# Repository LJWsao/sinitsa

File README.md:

KiCAD files for the all band receiver. This can pick up strong local sources of RF such as AM and FM radio stations. It is based on the 
Amazing All Band Receiver by Charles Wenzel: https://techlib.com/electronics/allband.htm

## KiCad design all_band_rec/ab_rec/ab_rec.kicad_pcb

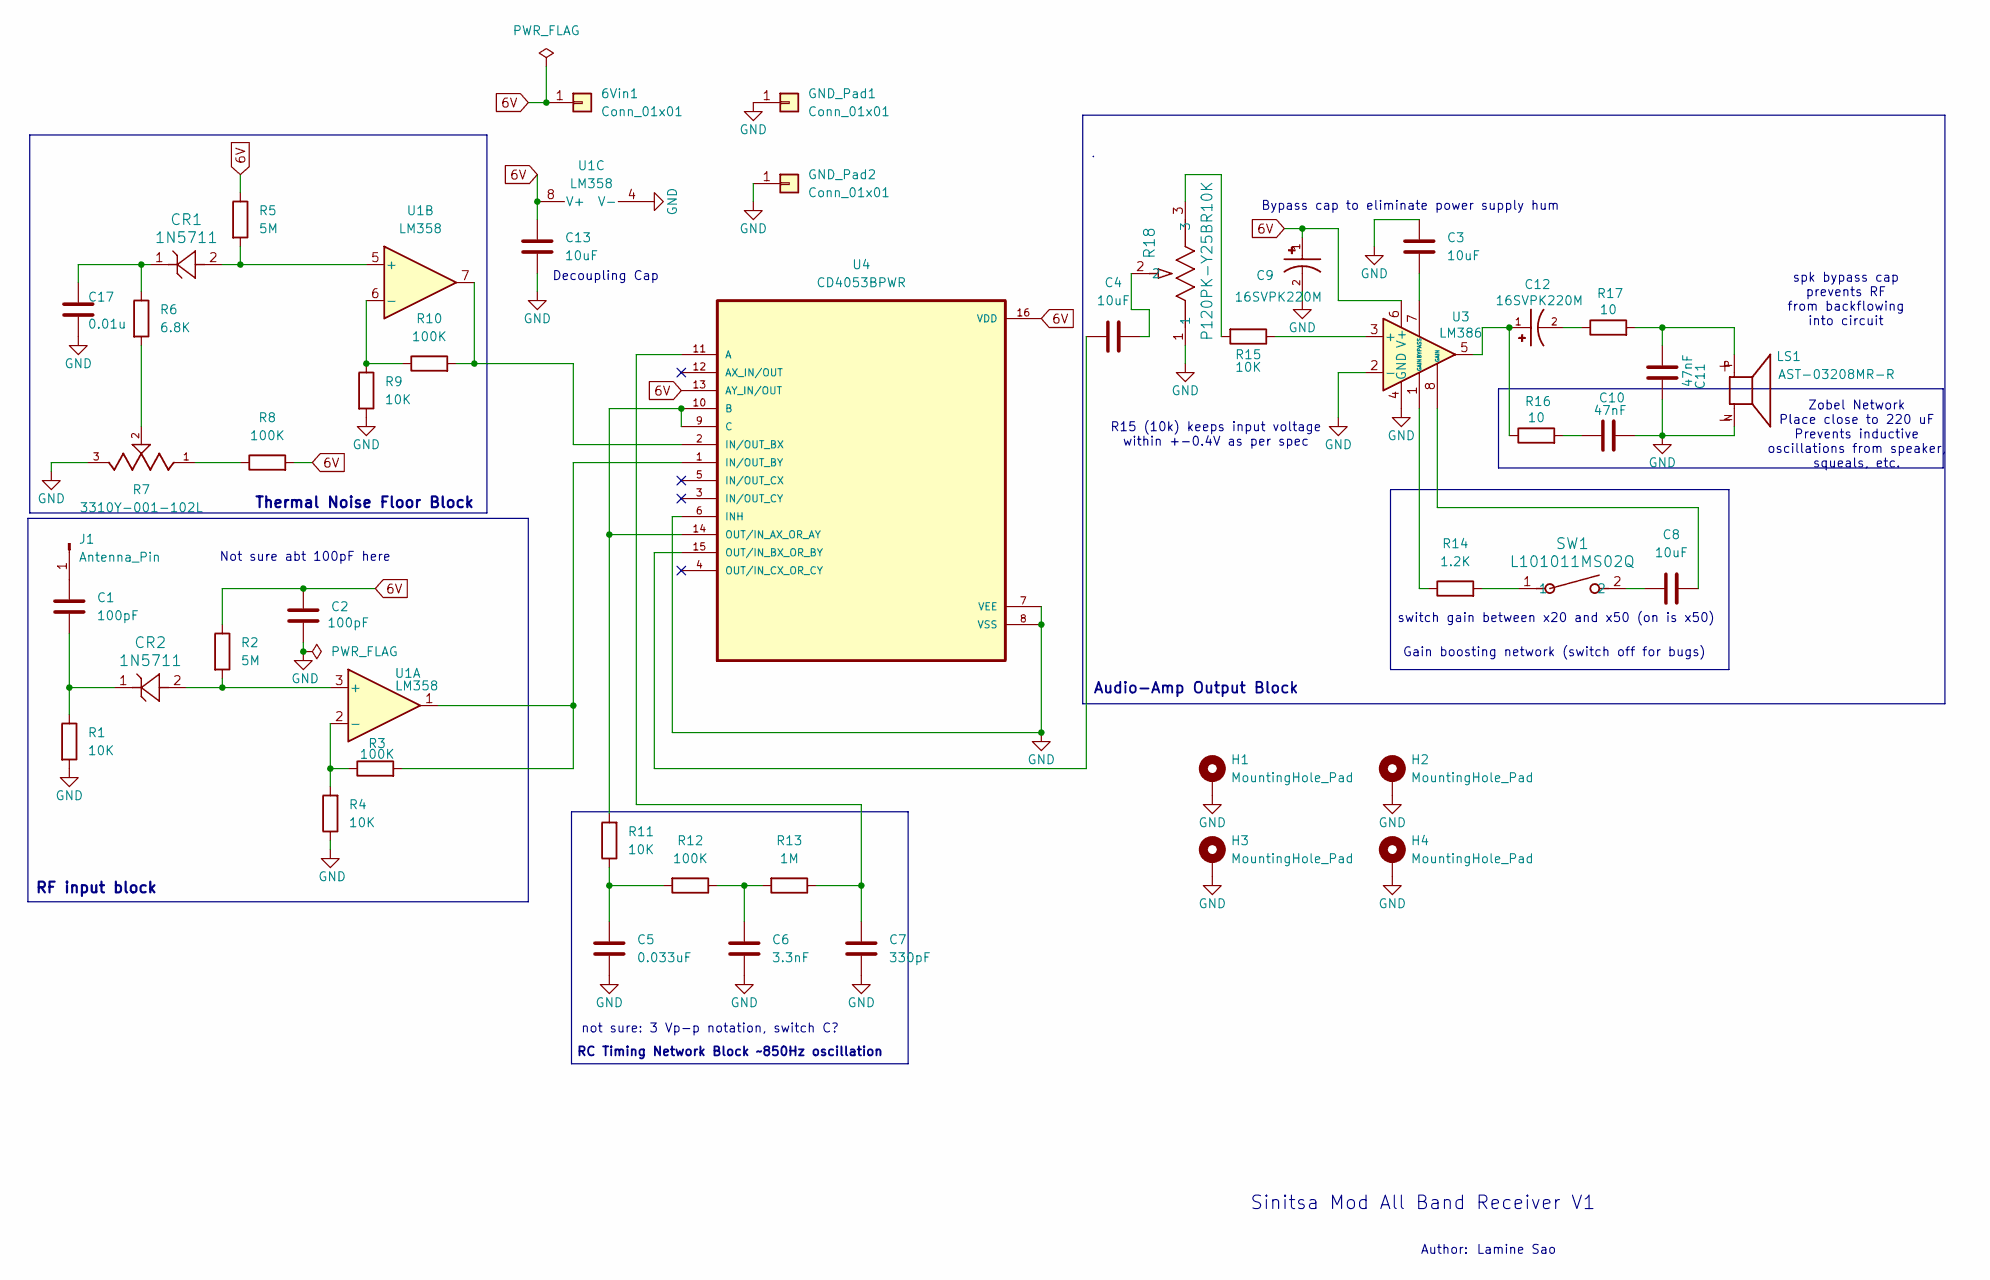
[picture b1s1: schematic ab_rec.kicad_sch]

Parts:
6Vin1: Conn_01x01; TestPoint_Pad_3.0x3.0mm
C1, C2: 100pF; C_0603_1608Metric_Pad1.08x0.95mm_HandSolder
C3, C4, C8, C13: 10uF; C_0805_2012Metric_Pad1.18x1.45mm_HandSolder
C5: 0.033uF; C_0805_2012Metric_Pad1.18x1.45mm_HandSolder
C6: 3.3nF; C_0603_1608Metric_Pad1.08x0.95mm_HandSolder
C7: 330pF; C_0603_1608Metric_Pad1.08x0.95mm_HandSolder
C9, C12: 16SVPK220M; CAP_16SVPK220M; PARTREV 28-Jun-19
C10, C11: 47nF; C_0603_1608Metric_Pad1.08x0.95mm_HandSolder
C17: 0.01u; C_0603_1608Metric
CR1, CR2: 1N5711; DO-35_STM_5711
GND_Pad1, GND_Pad2: Conn_01x01; TestPoint_Pad_3.0x3.0mm
H1, H2, H3, H4: MountingHole_Pad; MountingHole_3.5mm_Pad_Via
J1: Antenna_Pin; TestPoint_Pad_3.0x3.0mm
LS1: AST-03208MR-R; SPKR_AST-03208MR-R; PARTREV C
R1, R4, R9, R11, R15: 10K; R_0805_2012Metric_Pad1.20x1.40mm_HandSolder
R2, R5: 5M; R_0805_2012Metric_Pad1.20x1.40mm_HandSolder
R3, R10, R12: 100K; R_0805_2012Metric_Pad1.20x1.40mm_HandSolder
R6: 6.8K; R_0805_2012Metric_Pad1.20x1.40mm_HandSolder
R7: 3310Y-001-102L; POT_TRIM_3310Y-001-102L
R8: 100K; R_1206_3216Metric_Pad1.30x1.75mm_HandSolder
R13: 1M; R_1206_3216Metric_Pad1.30x1.75mm_HandSolder
R14: 1.2K; R_1206_3216Metric_Pad1.30x1.75mm_HandSolder
R16, R17: 10; R_1206_3216Metric_Pad1.30x1.75mm_HandSolder
R18: P120PK-Y25BR10K; POT_P120PK-x25_TTE
SW1: L101011MS02Q; SW_1MS02Q_CNK_Slide_Switch
U1: LM358; lm358-D8-L
U3: LM386
U4: CD4053BPWR; SOP65P640X120-16N

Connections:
6V: 6Vin1.1, C2.1, C9.1, C13.1, R2.1, R5.1, R8.2, U1.8 (V+), U3.6 (V+), U4.13 (AY_IN/OUT), U4.16 (VDD)
GND: C2.2, C3.2, C5.1, C6.1, C7.1, C9.2, C10.2, C11.2, C13.2, C17.2, GND_Pad1.1, GND_Pad2.1, H1.1, H2.1, H3.1, H4.1, LS1.N, R1.2, R4.1, R7.3, R9.2, R18.1, U1.4 (V-), U3.2 (-), U3.4 (GND), U4.6 (INH), U4.7 (VEE), U4.8 (VSS); also elsewhere on the board
unnamed: C1.2, CR2.1, R1.1
unnamed: C4.2, R18.2
unnamed: C5.2, R11.1, R12.2
unnamed: C6.2, R12.1, R13.2
unnamed: C8.1, SW1.2
unnamed: C8.2, U3.8 (GAIN)
unnamed: C10.1, R16.2
unnamed: C11.1, LS1.P, R17.2
unnamed: C12.1, R16.1, U3.5
unnamed: C12.2, R17.1
unnamed: C17.1, CR1.1, R6.1
unnamed: C1.1, J1.1
unnamed: R6.2, R7.2
unnamed: R7.1, R8.1
unnamed: R14.1, U3.1 (GAIN)
unnamed: R14.2, SW1.1
unnamed: R15.2, R18.3
unnamed: CR2.2, R2.2, U1.3 (+)
unnamed: R3.1, R4.2, U1.2 (-)
unnamed: CR1.2, R5.2, U1.5 (+)
unnamed: R9.1, R10.1, U1.6 (-)
unnamed: R15.1, U3.3 (+)
unnamed: C3.1, U3.7 (BYPASS)
unnamed: C7.2, R13.1, U4.11 (A)
unnamed: R11.2, U4.9 (C), U4.10 (B), U4.14 (OUT/IN_AX_OR_AY)
unnamed: R10.2, U1.7, U4.2 (IN/OUT_BX)
unnamed: R3.2, U1.1, U4.1 (IN/OUT_BY)
unnamed: C4.1, U4.15 (OUT/IN_BX_OR_BY)

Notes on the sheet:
Zobel Network Place close to 220 uF Prevents inductive oscillations from speaker, squeals, etc.
Decoupling Cap
Thermal Noise Floor Block
Lamine Sao
Bypass cap to eliminate power supply hum
not sure: 3 Vp-p notation, switch C?
R15 (10k) keeps input voltage within +-0.4V as per spec
switch gain between x20 and x50 (on is x50)
Author:
Gain boosting network (switch off for bugs)
RF input block
Audio-Amp Output Block
RC Timing Network Block ~850Hz oscillation
spk bypass cap prevents RF from backflowing into circuit
Not sure abt 100pF here
Sinitsa Mod All Band Receiver V1

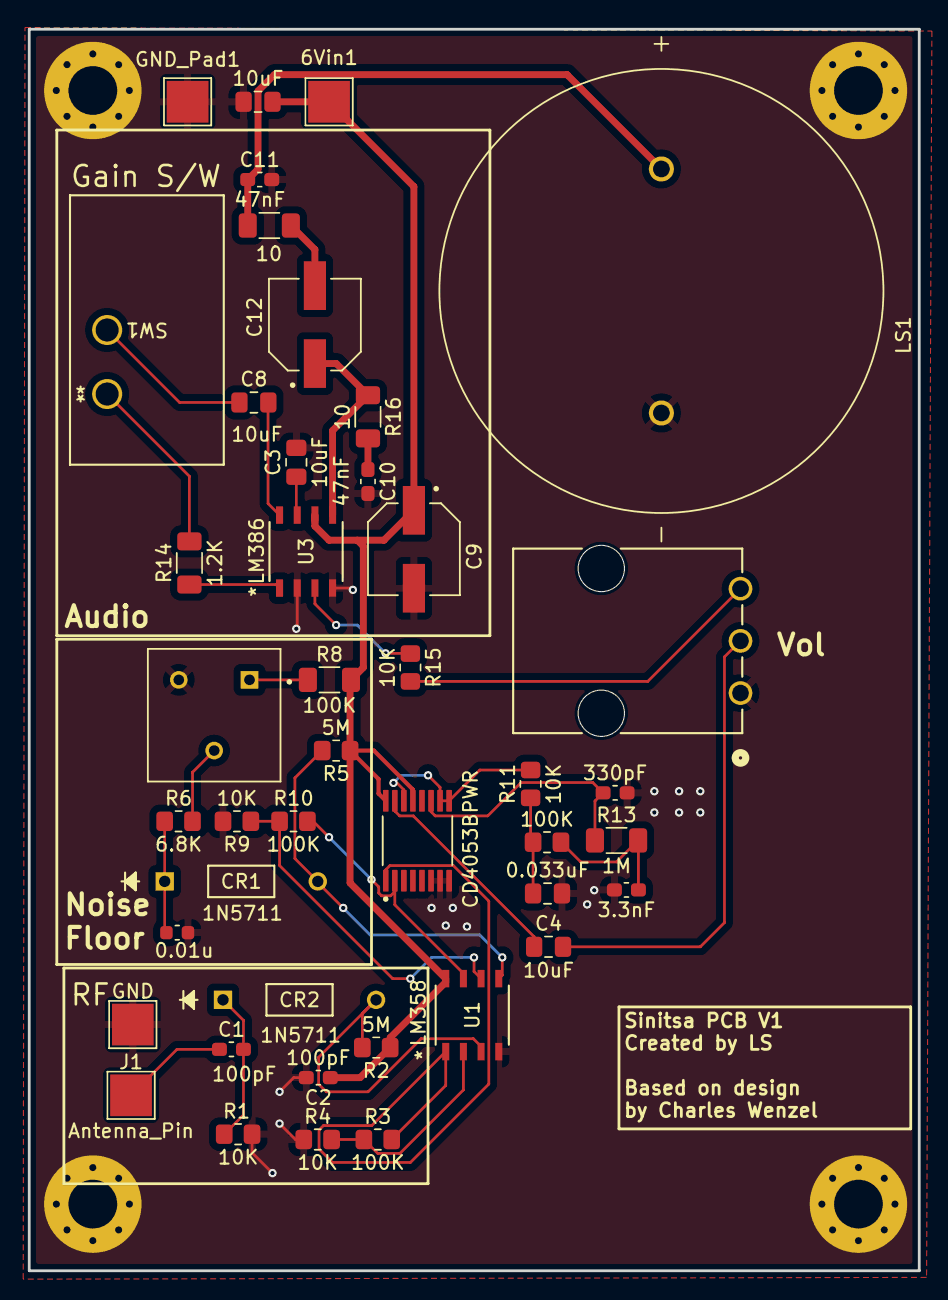
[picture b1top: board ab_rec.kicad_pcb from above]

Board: 2 copper layers, 63.9 x 89.2 mm, 47 parts (0 on the bottom side), 30 nets.

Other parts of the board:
GND: Conn_01x01; TestPoint_Pad_3.0x3.0mm

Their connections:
GND: GND.1; also elsewhere on the board

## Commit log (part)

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2026-04-02 edits backups
2026-04-02 schematic update
2026-05-03 Schematic updates
2026-05-03 Completed schematic, still finishing footprints
2026-05-03 fixed (maybe?) audio output section
2026-06-17 Minor schematic changes (fixed zobel, added more decoupling caps), still having ERC Power rules be sad
2026-06-17 Added footprints and symbols, 3D models for SPST slide switch and 1N5711 diodes
2026-06-18 Added all footprints, most 3D models, ERC rules check runs with no errors or warnings :)
2026-06-18 minor change and backup
2026-06-19 fixed switch to match numbering between footprint and symbol
2026-06-19 final backup for the night
2026-06-22 Added symbols, footprints, and models for lin pots and speaker
2026-06-22 All footprints and symbols updated properly, started pcb layout
2026-06-22 pcb layout organization
